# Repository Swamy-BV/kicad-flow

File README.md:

# KiCadFlow

Build KiCad schematics and PCBs through MCP. Small, composable tools handle
file formats and geometry; the caller controls placement, wiring, and routing.

<p align="center">

</p>

## Quick start

Requires Windows, Python 3.10+, and a KiCad 11 nightly (10.99).
`kicad11` tracks the IPC migration; the previous backend is on `kicad10`.
Schematic and PCB primitives edit native objects directly through IPC.

```powershell
python -m venv .venv
.\.venv\Scripts\python.exe -m pip install -e .
python scripts/install_kicad_ipc.py
$env:KICAD_FLOW_IPC_PYTHON = (Resolve-Path out/kicad-ipc/venv/Scripts/python.exe).Path
.\.venv\Scripts\python.exe -m kicad_flow.server doctor
.\.venv\Scripts\python.exe -m kicad_flow.server
```

Set `KICAD_FLOW_KICAD_CLI` to the nightly's `kicad-cli.exe` when several versions
are installed. Editing defaults to an owned headless editor. Set
`KICAD_FLOW_SCHEMATIC_MODE=gui` or `KICAD_FLOW_PCB_MODE=gui` to edit an
already-open document live, with KiCad's IPC server enabled.
See [schematic](src/kicad_flow/backend/kicad/schematic/README.md) and
[PCB IPC notes](src/kicad_flow/backend/kicad/pcb/README.md) for current limitations.

For an MCP client, use the virtual environment's Python executable with
arguments `-m kicad_flow.server`. Add `--http` for
`http://127.0.0.1:8471/mcp`, or `--tool-search` for on-demand tool discovery.

## Capabilities

- **Schematics:** components, wiring, labels, hierarchy, footprint assignment, ERC.
- **PCB:** schematic synchronization, placement, copper, outlines, DRC.
- **Review:** connectivity, geometry, proposed-change checks, 2D and 3D renders.
- **Manufacturing:** JLCPCB profiles, Gerbers, drills, BOM/CPL, checked packages.
- **Routing:** FreeRouting design export and native session import into a checked copy.

Coordinates are in millimetres. Check connectivity, ERC, DRC, and renders before
fabrication. See [JLCPCB setup](src/kicad_flow/providers/jlcpcb/README.md) for the
optional local parts catalogue.

## Examples

<table>
  <tr>
    <td width="50%" align="center">
      <br>
      <strong><a href="examples/led_digits/">LED digits</a></strong><br>
      Schematic, PCB, and routing.
    </td>
    <td width="50%" align="center">
      <br>
      <strong><a href="examples/batman/">Batman</a></strong><br>
      Shaped LED board.
    </td>
  </tr>
  <tr>
    <td width="50%" align="center">
      <br>
      <strong><a href="examples/art_board/">Mooncat art board</a></strong><br>
      PCB artwork on both sides.
    </td>
    <td width="50%" align="center">
      <br>
      <strong><a href="examples/esc4in1/">4-in-1 ESC</a></strong><br>
      Placement exercise; not ready for fabrication.
    </td>
  </tr>
</table>

The [flight controller](examples/fc/) demonstrates a hierarchical STM32 schematic.
For the default five-item limit, see
[staged board transfer](docs/staged-board-transfer.md) and run
`python examples/scripts/staged_board_transfer.py`.
Run the larger examples with an explicit batch limit:

```powershell
$env:KICAD_FLOW_BATCH_LIMIT = "1000"
python examples/scripts/led_digits.py
```

## Dashboard

Open [localhost:8472](http://localhost:8472) for live preview and tool activity.
Schematic and PCB tabs keep inspection snapshots until you refresh them.

The native chat companion opens beside your KiCad project. Edits appear live in
the actual schematic and PCB editors through GUI IPC. It reuses your local Codex
account or opens ChatGPT sign-in. Requires Codex CLI on `PATH` and KiCad IPC enabled.

```powershell
python -m kicad_flow.gui C:\Projects\MyBoard\MyBoard.kicad_pro
python -m kicad_flow.agent login
python -m kicad_flow.agent run "Inspect the schematic" --ask
```

The CLI automatically connects to an open companion and shares its conversation.
Closing chat leaves KiCad open. The dashboard remains separate on port 8472.

## Development

MCP startup instructions are compact; detailed workflows are loaded on demand
through resources or `get_workflow`. See [context delivery](docs/mcp-context.md).

```powershell
python -m ruff check .
python -m mypy
python scripts/codeql.py
$env:KICAD_FLOW_BATCH_LIMIT = "1000"
python examples/scripts/fc.py
python examples/scripts/led_digits.py
```

Examples are the integration checks. Contributor guidance is in [AGENTS.md](AGENTS.md).
The CodeQL command installs the pinned official bundle and writes SARIF and a
summary under `out/codeql/`; findings return a nonzero exit code.
For a Windows bundle, run `packaging/windows/build.ps1`; distribute the entire
`dist/kicad-flow` directory. KiCad remains required.

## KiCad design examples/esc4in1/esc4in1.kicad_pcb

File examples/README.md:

# Examples

Six designs, each one a script in [`scripts/`](scripts/) that builds a folder
next to it. **Every one reports 0 ERC errors and 0 warnings.**

The scripts are the source; the folders are output. Rebuild any of them:

```bash
python examples/scripts/fc_via_mcp.py
```

| example | script | files | nets | what it shows |
| --- | --- | --- | --- | --- |
| [`mcp_sheet`](mcp_sheet/) | `draw_via_mcp.py` | 1 | 5 | the smallest one: a 5 V → 3.3 V regulator |
| [`usbc_3v3`](usbc_3v3/) | `usbc_via_mcp.py` | 1 | 14 | USB-C in, both CC pulldowns, polyfuse then TVS, one ground rail |
| [`dual_buffer`](dual_buffer/) | `dual_buffer_via_mcp.py` | 1 | 10 | an LM358 — a multi-unit symbol, three units sharing one reference |
| [`usb_ttl4`](usb_ttl4/) | `usb_ttl4_via_mcp.py` | 1 | 55 | an FT4232H four-channel USB-to-TTL adapter, 64 pins |
| [`multisheet`](multisheet/) | `multisheet_via_mcp.py` | 4 | 8 | a hierarchy: signals cross by port, power crosses by name |
| [`fc`](fc/) | `fc_via_mcp.py` | 5 | 76 | an STM32F405 flight controller, crossing sheets by global label |

## How to read them

Every script drives the MCP server and nothing else. It **chooses every
coordinate itself** and asks the server only for facts — where a pin is, what a
symbol's box measures, what the sheet actually connects. There is no autoplacer
and no wire router to reach for.

Each one ends by asking the sheet what it became, rather than assuming:

```python
report = await call("check_sheet", path=root)   # violations, by part and pin
nets   = await call("list_nets",   path=root)   # what is ACTUALLY connected
```

That pairing is the point. `check_sheet` catches the electrical half; the render
catches how it reads. Both are needed, and the second is still a human looking
at a picture.

Where a layout comes out badly, that is the finding — not a reason to reach past
the API. The comments in each script say which choices were deliberate and which
were mistakes worth keeping a note of.

## What each one taught

- **`dual_buffer`** — an LM358's three units share one reference and are placed
  one call at a time. Before `unit=` existed, all eight pins came back at one
  unit's coordinates and produced a silently wrong netlist.
- **`multisheet`** — power crosses a sheet boundary **by name** and signals
  cross **by port**. The power page has no ports at all despite feeding both
  other pages.
- **`fc`** — with twenty-two signals between pages, ports would turn the root
  into a wiring diagram of its own. Global labels say the same thing in one
  symbol, which is how real flight controller schematics are drawn.

## Other scripts

`drone_frame.py` and `jlc_lookup.py` are board-side utilities, not schematic
examples.

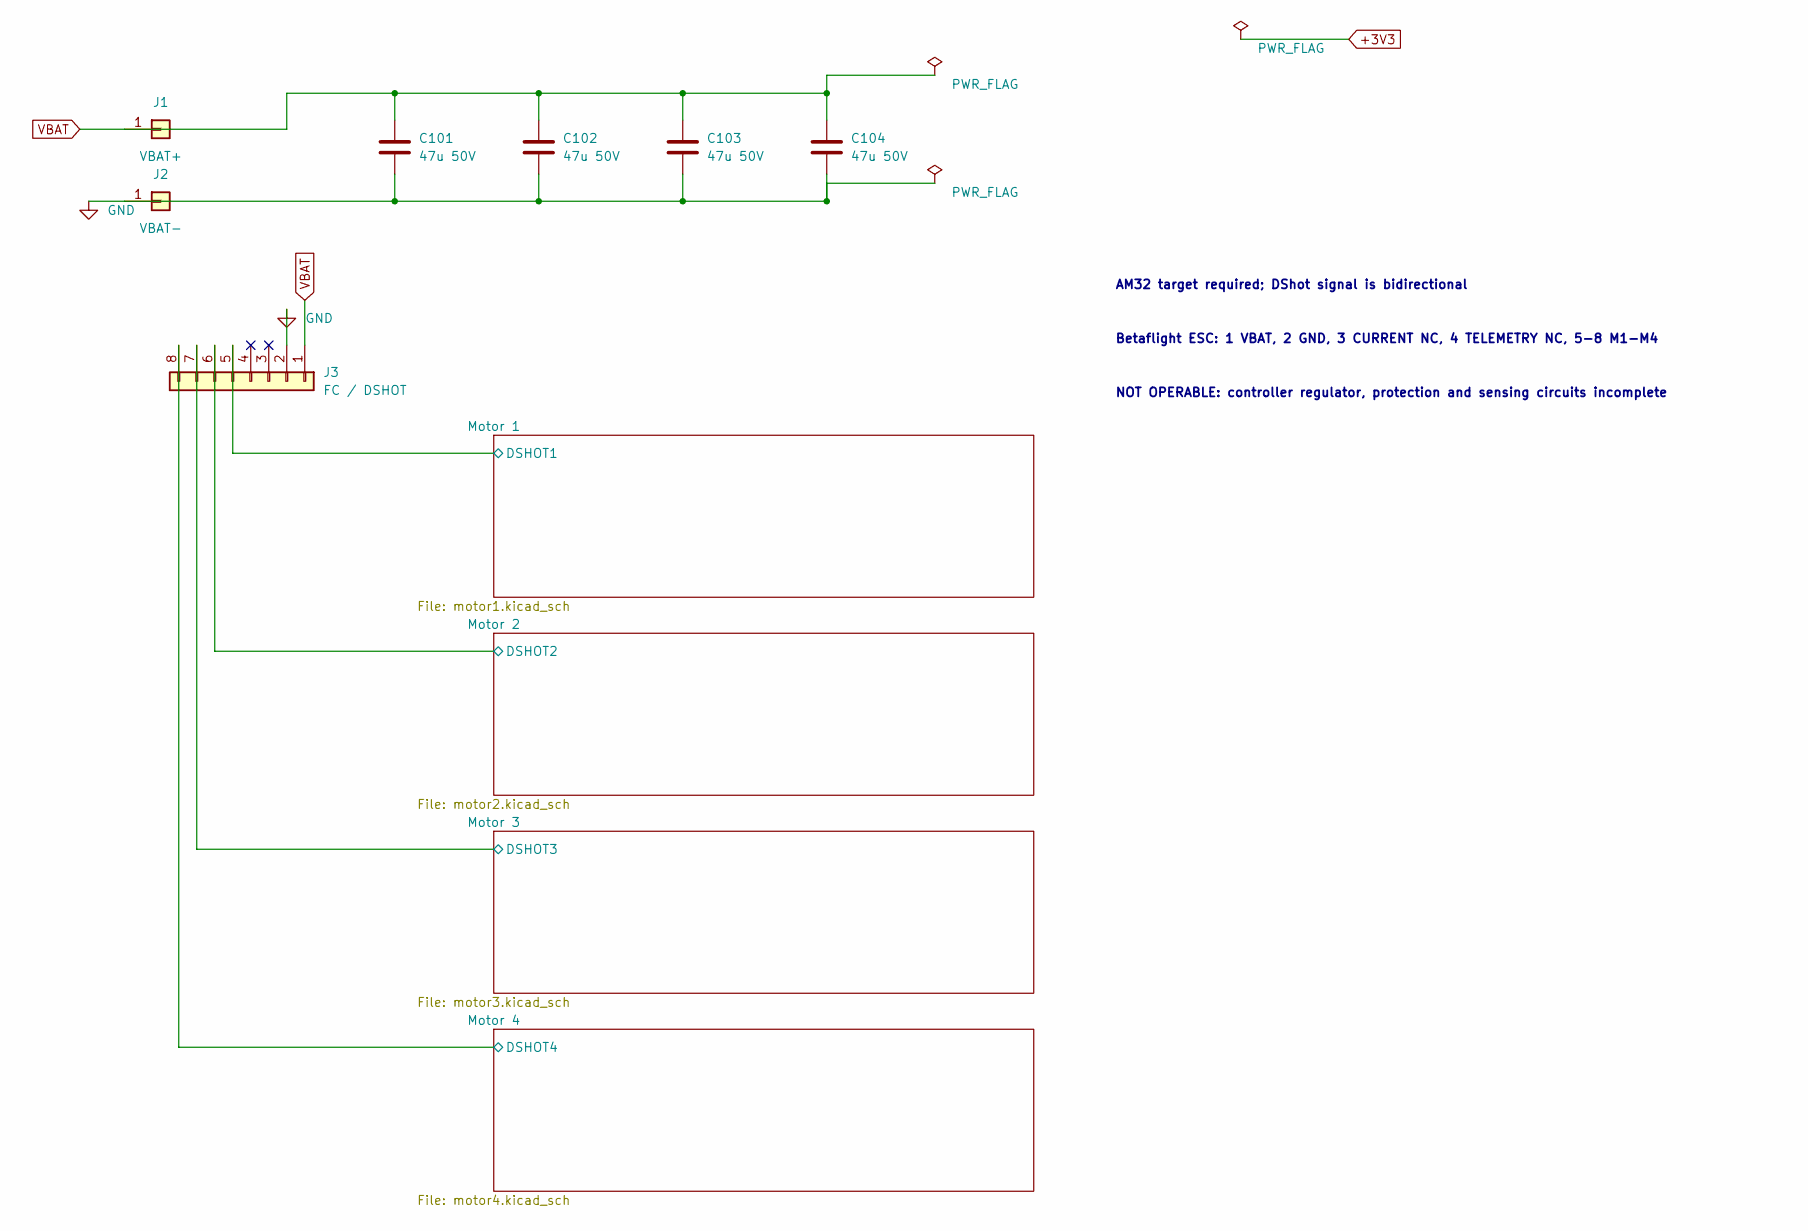
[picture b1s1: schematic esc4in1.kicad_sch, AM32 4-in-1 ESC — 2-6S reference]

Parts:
C101, C102, C103, C104: 47u 50V
J1: VBAT+
J2: VBAT-
J3: FC / DSHOT

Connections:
DSHOT1: J3.5; also elsewhere on the board
DSHOT2: J3.6; also elsewhere on the board
DSHOT3: J3.7; also elsewhere on the board
DSHOT4: J3.8; also elsewhere on the board
GND: C101.2, C102.2, C103.2, C104.2, J2.1, J3.2; also elsewhere on the board
VBAT: C101.1, C102.1, C103.1, C104.1, J1.1, J3.1; also elsewhere on the board

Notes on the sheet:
AM32 target required; DShot signal is bidirectional
Betaflight ESC: 1 VBAT, 2 GND, 3 CURRENT NC, 4 TELEMETRY NC, 5-8 M1-M4
NOT OPERABLE: controller regulator, protection and sensing circuits incomplete

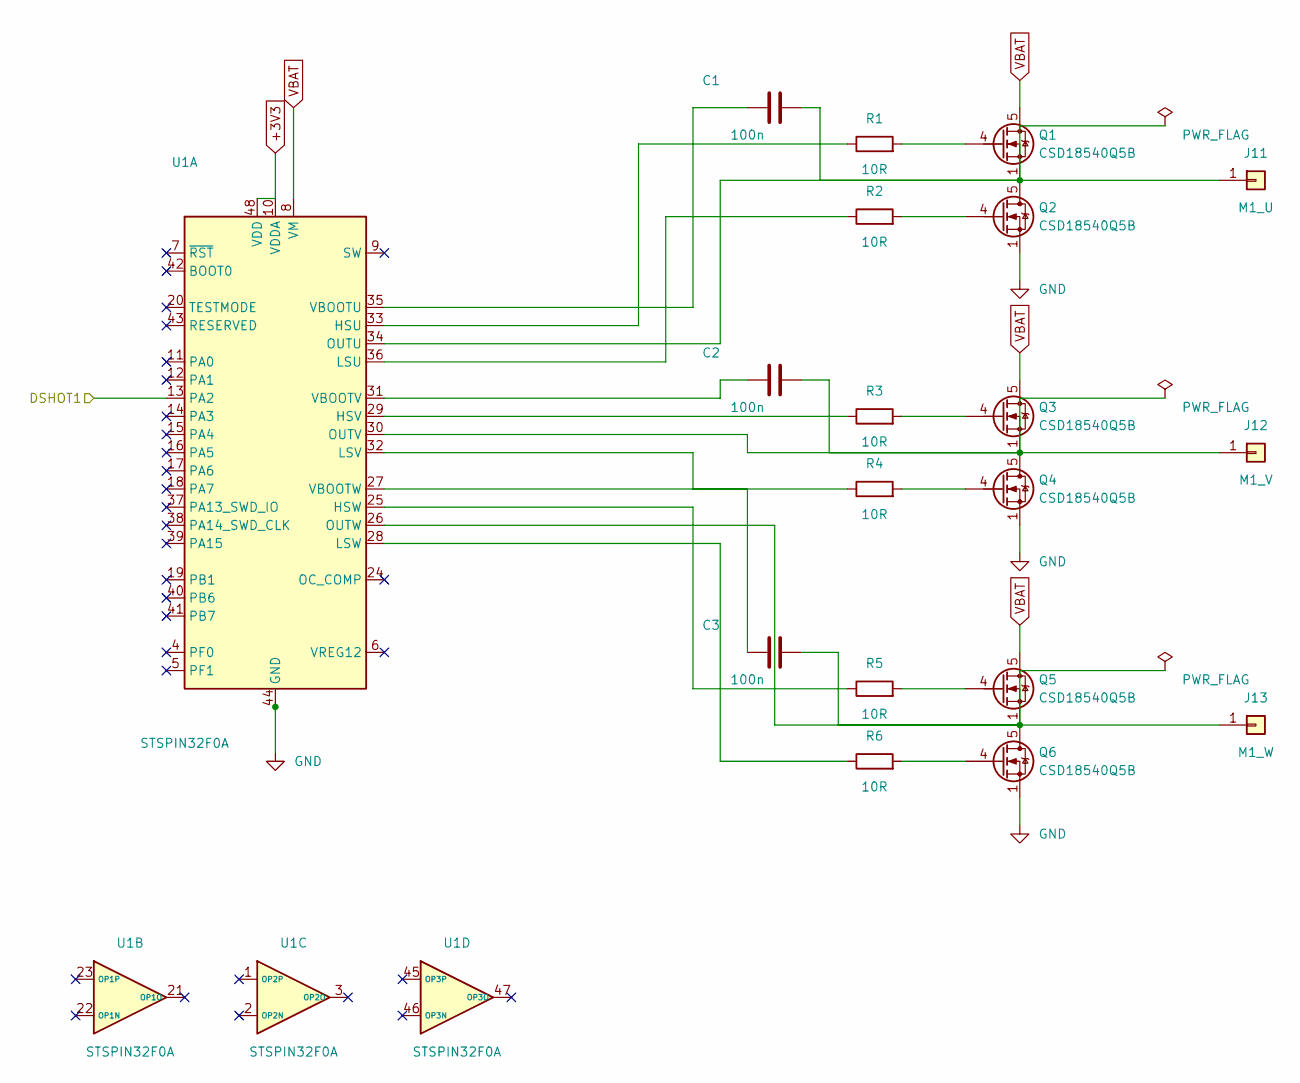
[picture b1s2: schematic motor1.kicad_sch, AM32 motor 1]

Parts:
C1, C2, C3: 100n
J11: M1_U
J12: M1_V
J13: M1_W
Q1, Q2, Q3, Q4, Q5, Q6: CSD18540Q5B
R1, R2, R3, R4, R5, R6: 10R
U1: STSPIN32F0A

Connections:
+3V3: U1.10 (VDDA), U1.48 (VDD); also elsewhere on the board
DSHOT1: U1.13 (PA2); also elsewhere on the board
GND: Q2.1 (S), Q2.2 (S), Q2.3 (S), Q4.1 (S), Q4.2 (S), Q4.3 (S), Q6.1 (S), Q6.2 (S), Q6.3 (S), U1.44 (GND), U1.49 (GND); also elsewhere on the board
M1_U: C1.2, J11.1, Q1.1 (S), Q1.2 (S), Q1.3 (S), Q2.5 (D), U1.34 (OUTU)
M1_U_BOOT: C1.1, U1.35 (VBOOTU)
M1_U_DH: R1.1, U1.33 (HSU)
M1_U_DL: R2.1, U1.36 (LSU)
M1_U_GH: Q1.4 (G), R1.2
M1_U_GL: Q2.4 (G), R2.2
M1_V: C2.2, J12.1, Q3.1 (S), Q3.2 (S), Q3.3 (S), Q4.5 (D), U1.30 (OUTV)
M1_V_BOOT: C2.1, U1.31 (VBOOTV)
M1_V_DH: R3.1, U1.29 (HSV)
M1_V_DL: R4.1, U1.32 (LSV)
M1_V_GH: Q3.4 (G), R3.2
M1_V_GL: Q4.4 (G), R4.2
M1_W: C3.2, J13.1, Q5.1 (S), Q5.2 (S), Q5.3 (S), Q6.5 (D), U1.26 (OUTW)
M1_W_BOOT: C3.1, U1.27 (VBOOTW)
M1_W_DH: R5.1, U1.25 (HSW)
M1_W_DL: R6.1, U1.28 (LSW)
M1_W_GH: Q5.4 (G), R5.2
M1_W_GL: Q6.4 (G), R6.2
VBAT: Q1.5 (D), Q3.5 (D), Q5.5 (D), U1.8 (VM); also elsewhere on the board

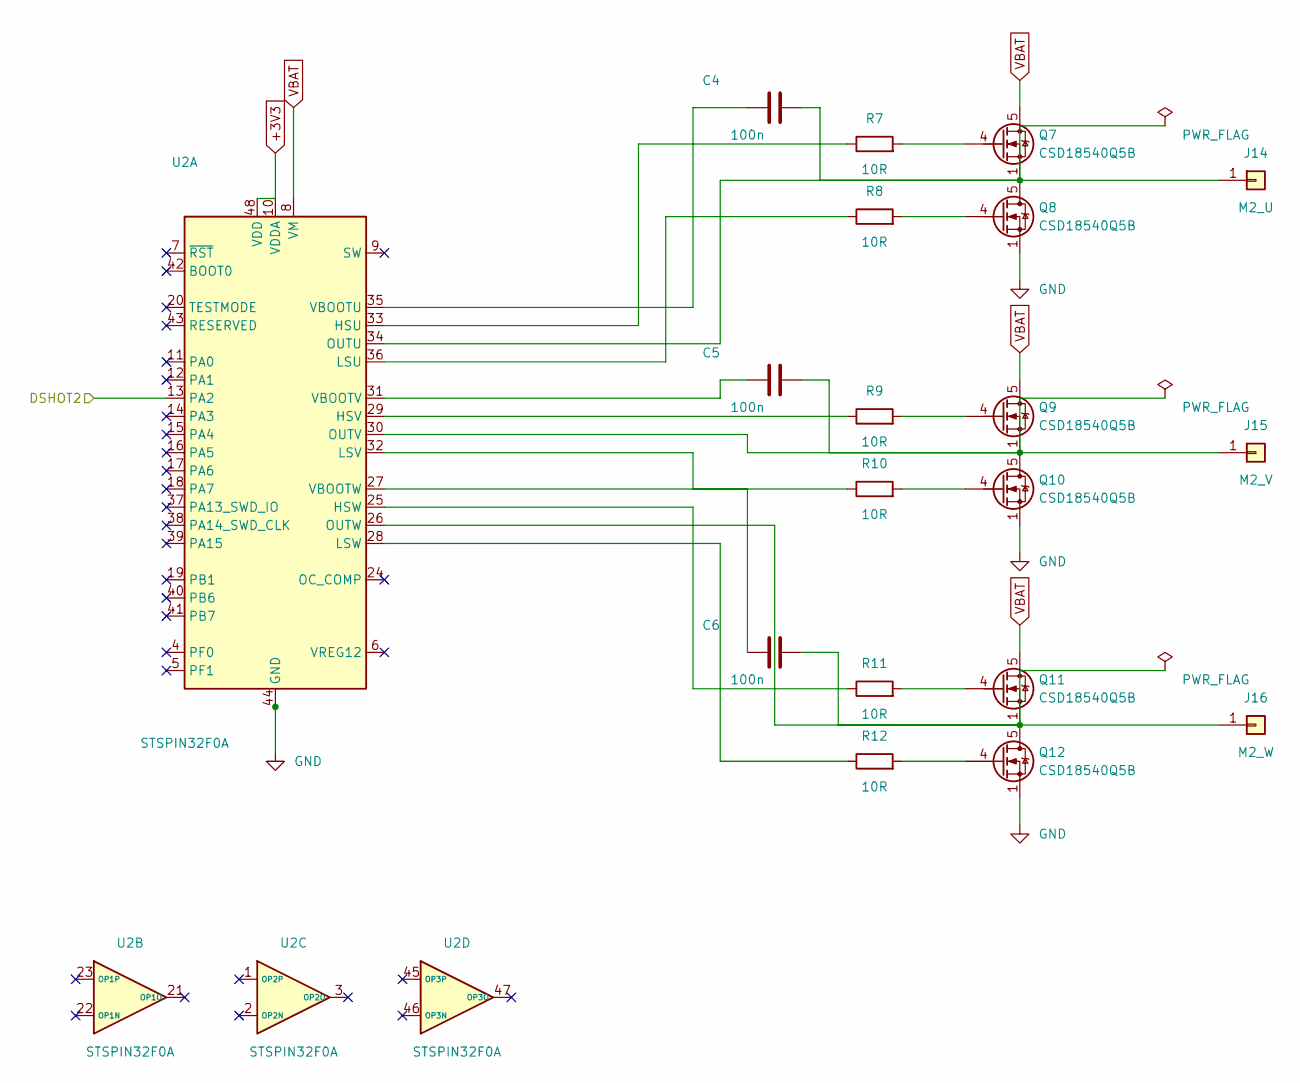
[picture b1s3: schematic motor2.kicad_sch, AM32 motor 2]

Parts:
C4, C5, C6: 100n
J14: M2_U
J15: M2_V
J16: M2_W
Q7, Q8, Q9, Q10, Q11, Q12: CSD18540Q5B
R7, R8, R9, R10, R11, R12: 10R
U2: STSPIN32F0A

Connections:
+3V3: U2.10 (VDDA), U2.48 (VDD); also elsewhere on the board
DSHOT2: U2.13 (PA2); also elsewhere on the board
GND: Q8.1 (S), Q8.2 (S), Q8.3 (S), Q10.1 (S), Q10.2 (S), Q10.3 (S), Q12.1 (S), Q12.2 (S), Q12.3 (S), U2.44 (GND), U2.49 (GND); also elsewhere on the board
M2_U: C4.2, J14.1, Q7.1 (S), Q7.2 (S), Q7.3 (S), Q8.5 (D), U2.34 (OUTU)
M2_U_BOOT: C4.1, U2.35 (VBOOTU)
M2_U_DH: R7.1, U2.33 (HSU)
M2_U_DL: R8.1, U2.36 (LSU)
M2_U_GH: Q7.4 (G), R7.2
M2_U_GL: Q8.4 (G), R8.2
M2_V: C5.2, J15.1, Q9.1 (S), Q9.2 (S), Q9.3 (S), Q10.5 (D), U2.30 (OUTV)
M2_V_BOOT: C5.1, U2.31 (VBOOTV)
M2_V_DH: R9.1, U2.29 (HSV)
M2_V_DL: R10.1, U2.32 (LSV)
M2_V_GH: Q9.4 (G), R9.2
M2_V_GL: Q10.4 (G), R10.2
M2_W: C6.2, J16.1, Q11.1 (S), Q11.2 (S), Q11.3 (S), Q12.5 (D), U2.26 (OUTW)
M2_W_BOOT: C6.1, U2.27 (VBOOTW)
M2_W_DH: R11.1, U2.25 (HSW)
M2_W_DL: R12.1, U2.28 (LSW)
M2_W_GH: Q11.4 (G), R11.2
M2_W_GL: Q12.4 (G), R12.2
VBAT: Q7.5 (D), Q9.5 (D), Q11.5 (D), U2.8 (VM); also elsewhere on the board

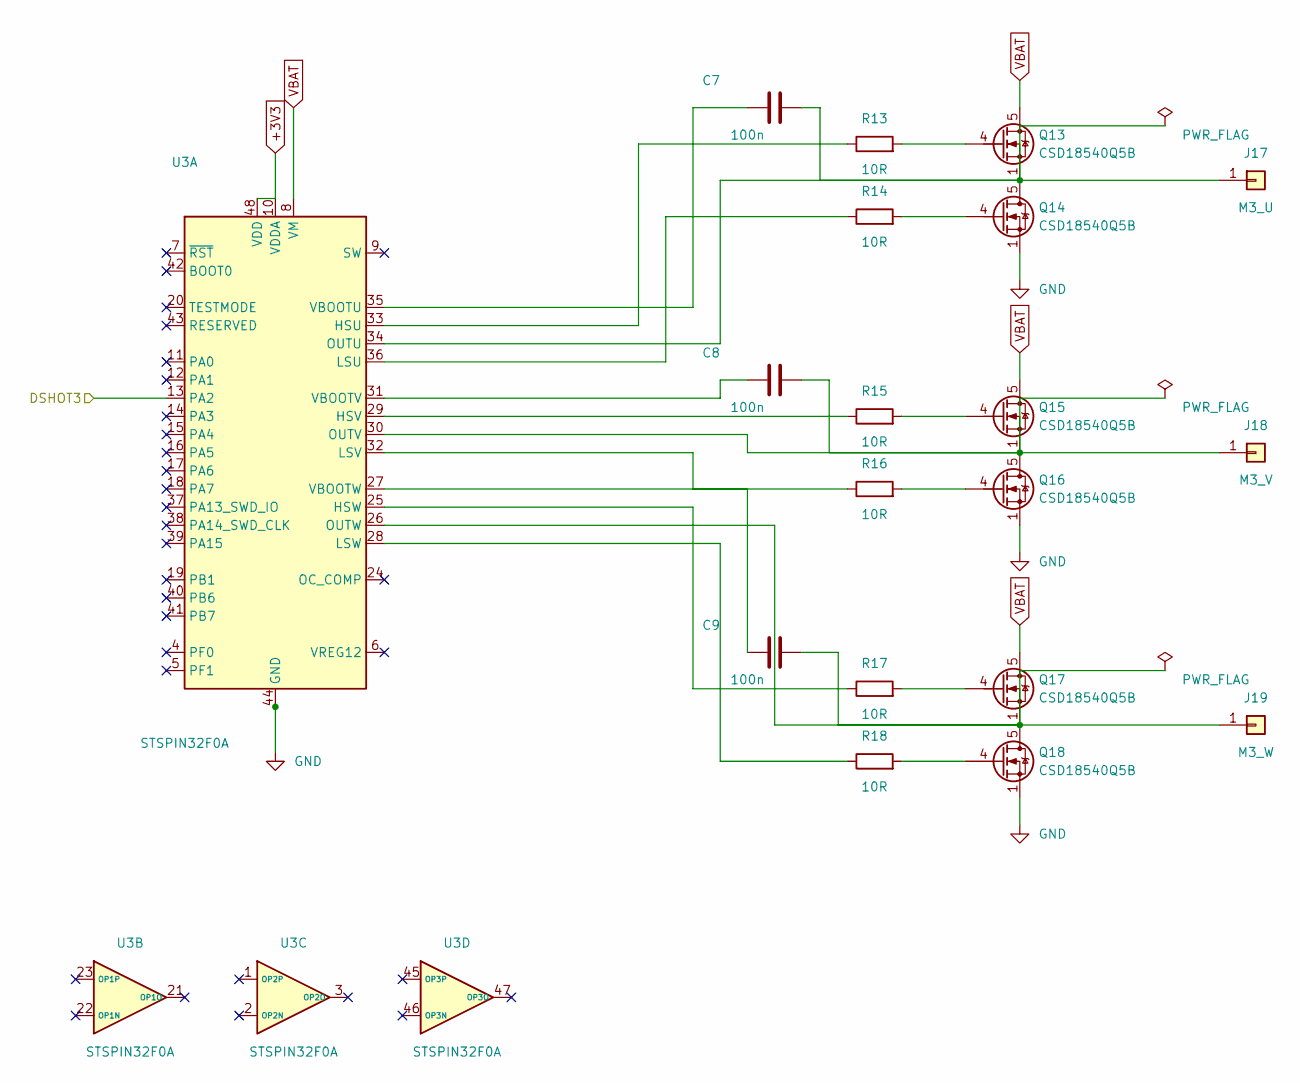
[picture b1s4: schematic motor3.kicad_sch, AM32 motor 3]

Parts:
C7, C8, C9: 100n
J17: M3_U
J18: M3_V
J19: M3_W
Q13, Q14, Q15, Q16, Q17, Q18: CSD18540Q5B
R13, R14, R15, R16, R17, R18: 10R
U3: STSPIN32F0A

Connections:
+3V3: U3.10 (VDDA), U3.48 (VDD); also elsewhere on the board
DSHOT3: U3.13 (PA2); also elsewhere on the board
GND: Q14.1 (S), Q14.2 (S), Q14.3 (S), Q16.1 (S), Q16.2 (S), Q16.3 (S), Q18.1 (S), Q18.2 (S), Q18.3 (S), U3.44 (GND), U3.49 (GND); also elsewhere on the board
M3_U: C7.2, J17.1, Q13.1 (S), Q13.2 (S), Q13.3 (S), Q14.5 (D), U3.34 (OUTU)
M3_U_BOOT: C7.1, U3.35 (VBOOTU)
M3_U_DH: R13.1, U3.33 (HSU)
M3_U_DL: R14.1, U3.36 (LSU)
M3_U_GH: Q13.4 (G), R13.2
M3_U_GL: Q14.4 (G), R14.2
M3_V: C8.2, J18.1, Q15.1 (S), Q15.2 (S), Q15.3 (S), Q16.5 (D), U3.30 (OUTV)
M3_V_BOOT: C8.1, U3.31 (VBOOTV)
M3_V_DH: R15.1, U3.29 (HSV)
M3_V_DL: R16.1, U3.32 (LSV)
M3_V_GH: Q15.4 (G), R15.2
M3_V_GL: Q16.4 (G), R16.2
M3_W: C9.2, J19.1, Q17.1 (S), Q17.2 (S), Q17.3 (S), Q18.5 (D), U3.26 (OUTW)
M3_W_BOOT: C9.1, U3.27 (VBOOTW)
M3_W_DH: R17.1, U3.25 (HSW)
M3_W_DL: R18.1, U3.28 (LSW)
M3_W_GH: Q17.4 (G), R17.2
M3_W_GL: Q18.4 (G), R18.2
VBAT: Q13.5 (D), Q15.5 (D), Q17.5 (D), U3.8 (VM); also elsewhere on the board

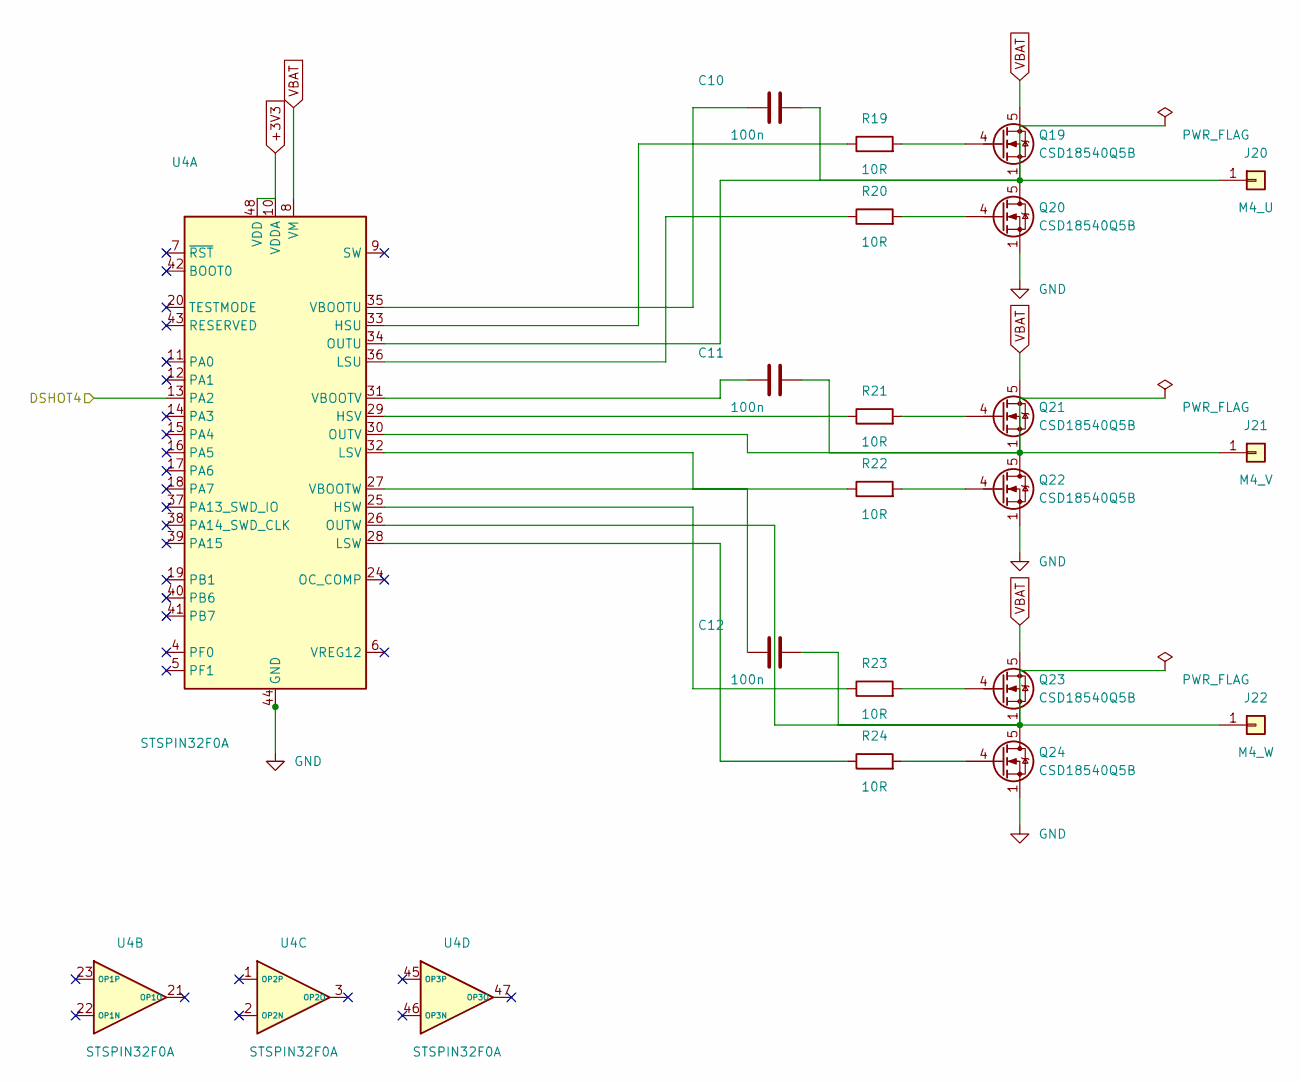
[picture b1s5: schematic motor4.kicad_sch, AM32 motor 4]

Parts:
C10, C11, C12: 100n
J20: M4_U
J21: M4_V
J22: M4_W
Q19, Q20, Q21, Q22, Q23, Q24: CSD18540Q5B
R19, R20, R21, R22, R23, R24: 10R
U4: STSPIN32F0A

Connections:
+3V3: U4.10 (VDDA), U4.48 (VDD); also elsewhere on the board
DSHOT4: U4.13 (PA2); also elsewhere on the board
GND: Q20.1 (S), Q20.2 (S), Q20.3 (S), Q22.1 (S), Q22.2 (S), Q22.3 (S), Q24.1 (S), Q24.2 (S), Q24.3 (S), U4.44 (GND), U4.49 (GND); also elsewhere on the board
M4_U: C10.2, J20.1, Q19.1 (S), Q19.2 (S), Q19.3 (S), Q20.5 (D), U4.34 (OUTU)
M4_U_BOOT: C10.1, U4.35 (VBOOTU)
M4_U_DH: R19.1, U4.33 (HSU)
M4_U_DL: R20.1, U4.36 (LSU)
M4_U_GH: Q19.4 (G), R19.2
M4_U_GL: Q20.4 (G), R20.2
M4_V: C11.2, J21.1, Q21.1 (S), Q21.2 (S), Q21.3 (S), Q22.5 (D), U4.30 (OUTV)
M4_V_BOOT: C11.1, U4.31 (VBOOTV)
M4_V_DH: R21.1, U4.29 (HSV)
M4_V_DL: R22.1, U4.32 (LSV)
M4_V_GH: Q21.4 (G), R21.2
M4_V_GL: Q22.4 (G), R22.2
M4_W: C12.2, J22.1, Q23.1 (S), Q23.2 (S), Q23.3 (S), Q24.5 (D), U4.26 (OUTW)
M4_W_BOOT: C12.1, U4.27 (VBOOTW)
M4_W_DH: R23.1, U4.25 (HSW)
M4_W_DL: R24.1, U4.28 (LSW)
M4_W_GH: Q23.4 (G), R23.2
M4_W_GL: Q24.4 (G), R24.2
VBAT: Q19.5 (D), Q21.5 (D), Q23.5 (D), U4.8 (VM); also elsewhere on the board

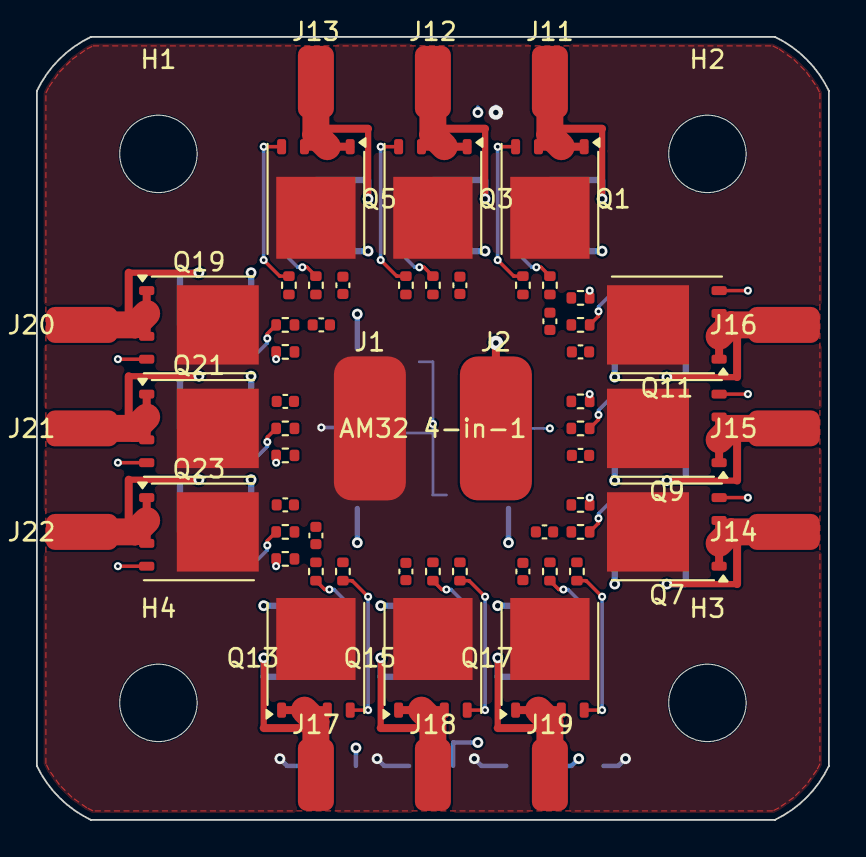
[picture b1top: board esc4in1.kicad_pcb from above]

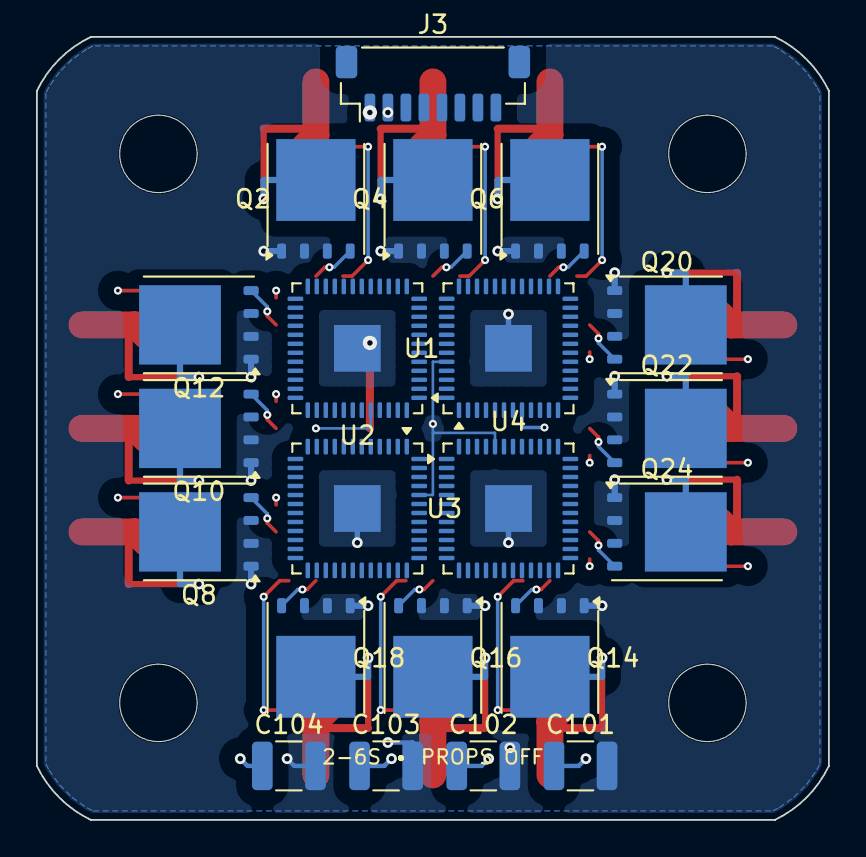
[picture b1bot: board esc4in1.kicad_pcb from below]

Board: 4 copper layers, 44.0 x 43.5 mm, 87 parts (21 on the bottom side), 79 nets.

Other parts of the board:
H1, H2, H3, H4: M4; MountingHole_4.3mm_M4

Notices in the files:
README.md:
AGPL 3.0 license
